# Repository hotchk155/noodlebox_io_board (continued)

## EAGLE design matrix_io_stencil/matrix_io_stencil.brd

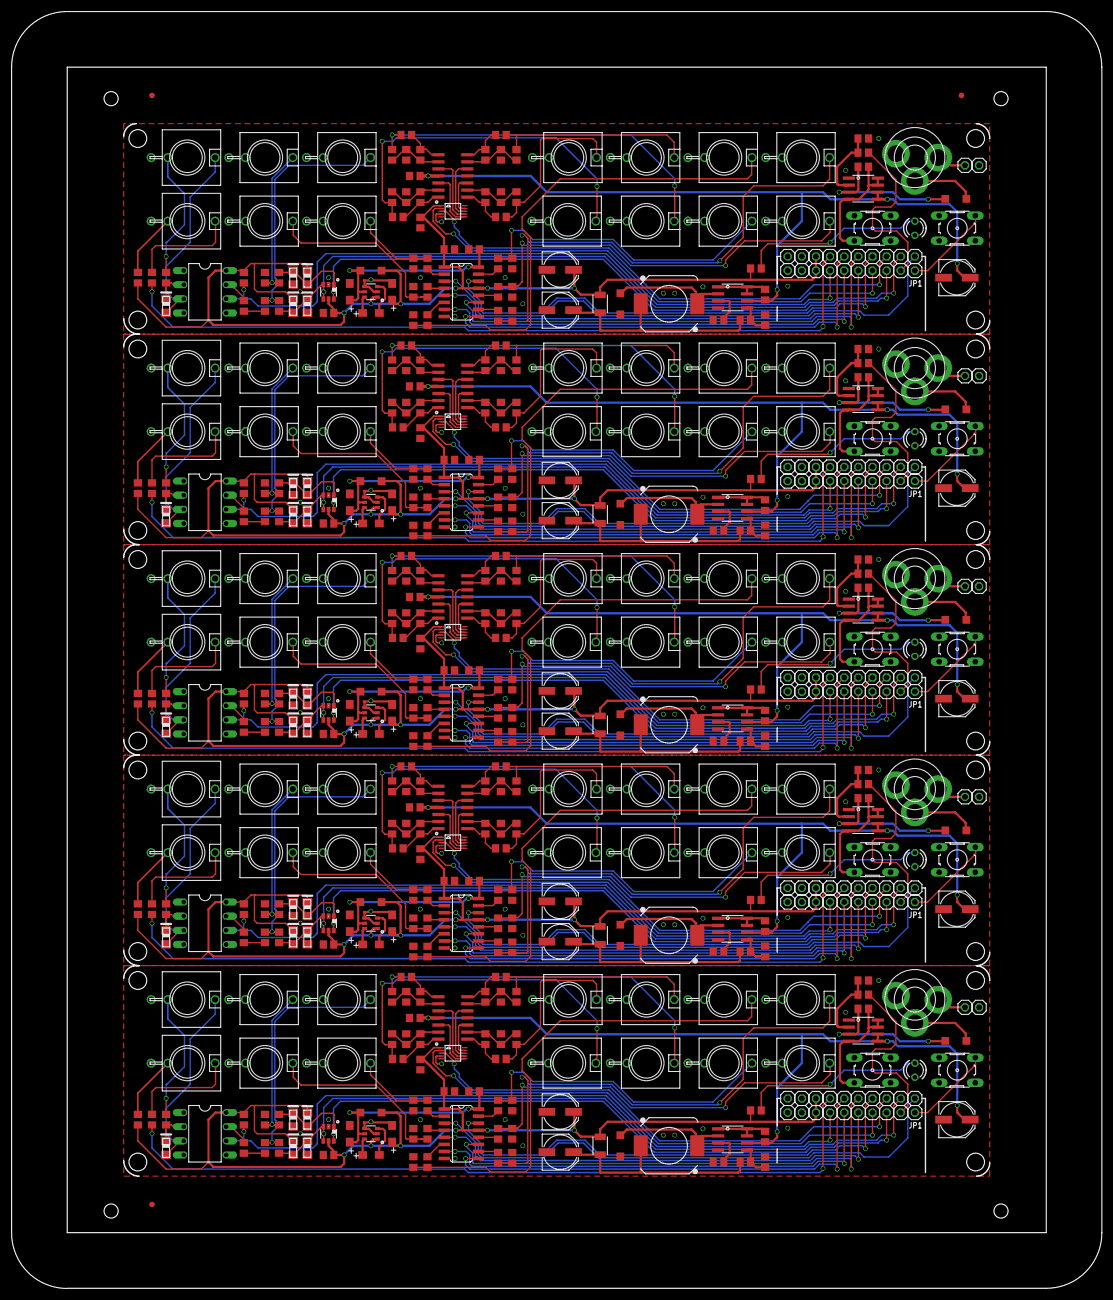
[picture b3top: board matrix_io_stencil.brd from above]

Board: 2 copper layers, 195.9 x 229.5 mm, 573 parts (0 on the bottom side), 345 nets.

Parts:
5V, 5V1, 5V2, 5V3, 5V4, 5V., 5V.1, 5V.2, 5V.3, 5V.4: 1X01
AUXI, AUXI1, AUXI2, AUXI3, AUXI4: WQP-PJ301M-12_JACK
AUXO, AUXO1, AUXO2, AUXO3, AUXO4: WQP-PJ301M-12_JACK
BT+, BT+1, BT+2, BT+3, BT+4: 1X01
BT-, BT-1, BT-2, BT-3, BT-4: 1X01
C1, C8, C9, C18, C24, C31, C32, C34, C46, C53, C54, C56, C68, C75, C76, C78, C90, C97, C98, C100: 100n; C0805
C2, C3, C4, C28, C29, C30, C50, C51, C52, C72, C73, C74, C94, C95, C96: 10u; SMC_A
C5, C6, C7, C10, C11, C12, C39, C40, C41, C42, C43, C44, C61, C62, C63, C64, C65, C66, C83, C84, C85, C86, C87, C88, C105, C106, C107, C108, C109, C110: 10n; C0805
C13, C35, C57, C79, C101: 20p; C0805
C14, C15, C16, C17, C23, C36, C37, C38, C45, C58, C59, C60, C67, C80, C81, C82, C89, C102, C103, C104: C0805
C19, C20, C22, C25, C27, C33, C47, C49, C55, C69, C71, C77, C91, C93, C99: PANASONIC_D
C21, C26, C48, C70, C92: 470p; C0805
CKI, CKI1, CKI2, CKI3, CKI4: WQP-PJ301M-12_JACK
CKO, CKO1, CKO2, CKO3, CKO4: WQP-PJ301M-12_JACK
CKOUT, CKOUT1, CKOUT2, CKOUT3, CKOUT4: 1X01
CLKIN, CLKIN1, CLKIN2, CLKIN3, CLKIN4: 1X01
CVA, CVA1, CVA2, CVA3, CVA4: WQP-PJ301M-12_JACK
CVB, CVB1, CVB2, CVB3, CVB4: WQP-PJ301M-12_JACK
CVC, CVC1, CVC2, CVC3, CVC4: WQP-PJ301M-12_JACK
CVD, CVD1, CVD2, CVD3, CVD4: WQP-PJ301M-12_JACK
D1, D2, D3, D4, D5, D9, D11, D12, D14, D15, D17, D19, D20, D22, D23, D25, D27, D28, D30, D31, D33, D35, D36, D38, D39: 0805DIODE
D6, D7, D8, D10, D13, D16, D18, D21, D24, D26, D29, D32, D34, D37, D40: MBR0520LT; SOD123
DC, DC1, DC2, DC3, DC4: PWR_SOCKET_2_1MM
E$1, E$2, E$3: FIDUCIAL_1MM
G1, G2, G3, G4, G5, G6, G7, G8, G9, G10, G11, G12, G13, G14, G15, G16, G17, G18, G19, G20: 1X01
GD1, GD2, GD3, GD4, GD5, GD6, GD7, GD8, GD9, GD10, GD11, GD12, GD13, GD14, GD15, GD16, GD17, GD18, GD19, GD20: 1X01
GT1, GT2, GT3, GT4, GT5, GT6, GT7, GT8, GT9, GT10, GT11, GT12, GT13, GT14, GT15, GT16, GT17, GT18, GT19, GT20: WQP-PJ301M-12_JACK
IC1, IC10, IC18, IC26, IC34: 6N138; DIL08
IC2, IC16, IC24, IC32, IC40: SN74LVC2G14; DBV_R-PDSO-G6
IC3, IC13, IC21, IC29, IC37: LM27675M5_CHARGEPUMP; SOT23-6
IC4, IC9, IC17, IC25, IC33: LM324D; SO14
IC5, IC11, IC19, IC27, IC35: MCP4728_QUAD_DAC; MSOP10
IC6, IC14, IC22, IC30, IC38: 4504D; SO16
IC7, IC12, IC20, IC28, IC36: SP34063A_BOOST_REG; SOIC8
IC8, IC15, IC23, IC31, IC39: FDS8958B; SOIC8
L1, L3, L5, L7, L9: 1210
L2, L4, L6, L8, L10: DR1030
MIDIIN, MIDIIN1, MIDIIN2, MIDIIN3, MIDIIN4: THONKICONN_STEREO; WQP-PJ301M-ST
MIDIOUT, MIDIOUT1, MIDIOUT2, MIDIOUT3, MIDIOUT4: THONKICONN_STEREO; WQP-PJ301M-ST
OFF, OFF1, OFF2, OFF3, OFF4: B3F-10XX
OFFSW, OFFSW1, OFFSW2, OFFSW3, OFFSW4: 1X01
ON, ON1, ON2, ON3, ON4: B3F-10XX
PWR, PWR1, PWR2, PWR3, PWR4: LED3MM
PWRCTL, PWRCTL1, PWRCTL2, PWRCTL3, PWRCTL4: 1X01
R1, R2, R3, R35, R38, R39, R69, R72, R73, R103, R106, R107, R137, R140, R141: 220; R0805
R4, R5, R36, R37, R70, R71, R104, R105, R138, R139: 1k8; R0805
R6, R8, R65, R68, R99, R102, R133, R136, R167, R170: 100k; R0805
R7, R9, R10, R11, R12, R13, R14, R15, R16, R19, R24, R27, R28, R30, R33, R40, R41, R42, R43, R53, R55, R56, R57, R58, R59, R60, R61, R63, R66, R67, R74, R75, R76, R77, R87, R89, R90, R91, R92, R93, R94, R95, R97, R100, R101, R108, R109, R110, R111, R121, R123, R124, R125, R126, R127, R128, R129, R131, R134, R135, R142, R143, R144, R145, R155, R157, R158, R159, R160, R161, R162, R163, R165, R168, R169: 1k; R0805
R17, R18, R20, R21, R22, R23, R25, R26, R44, R45, R46, R47, R48, R49, R50, R51, R78, R79, R80, R81, R82, R83, R84, R85, R112, R113, R114, R115, R116, R117, R118, R119, R146, R147, R148, R149, R150, R151, R152, R153: 10k/0.1%; R0805
R29, R52, R86, R120, R154: 0r33; R0805
R31, R54, R88, R122, R156: 3k; R0805
R32, R34, R62, R64, R96, R98, R130, R132, R164, R166: 10k; R0805
RSIN, RSIN1, RSIN2, RSIN3, RSIN4: 1X01
RSOUT, RSOUT1, RSOUT2, RSOUT3, RSOUT4: 1X01
RX, RX1, RX2, RX3, RX4: 1X01
SCL, SCL1, SCL2, SCL3, SCL4: 1X01
SDA, SDA1, SDA2, SDA3, SDA4: 1X01
TX, TX1, TX2, TX3, TX4: 1X01

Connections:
+5V: 5V.1, 5V..1, C1.1, C4.+, C8.1, C18.1, C19.+, D3.A, D4.A, D6.A, IC1.8, IC2.5, IC3.1, IC5.1, IC6.1, IC6.13, L1.2, R1.2, R4.2, R28.1
+5V1: 5V1.1, 5V.1.1, C24.1, C30.+, C31.1, C33.+, C34.1, D10.A, D11.A, D14.A, IC10.8, IC11.1, IC13.1, IC14.1, IC14.13, IC16.5, L3.2, R37.2, R38.2, R61.1
+5V2: 5V2.1, 5V.2.1, C46.1, C52.+, C53.1, C55.+, C56.1, D18.A, D19.A, D22.A, IC18.8, IC19.1, IC21.1, IC22.1, IC22.13, IC24.5, L5.2, R71.2, R72.2, R95.1
+5V3: 5V3.1, 5V.3.1, C68.1, C74.+, C75.1, C77.+, C78.1, D26.A, D27.A, D30.A, IC26.8, IC27.1, IC29.1, IC30.1, IC30.13, IC32.5, L7.2, R105.2, R106.2, R129.1
+5V4: 5V4.1, 5V.4.1, C90.1, C96.+, C97.1, C99.+, C100.1, D34.A, D35.A, D38.A, IC34.8, IC35.1, IC37.1, IC38.1, IC38.13, IC40.5, L9.2, R139.2, R140.2, R163.1
+9V: C14.1, C22.+, IC4.4, IC7.6, IC8.5, IC8.6, R29.1
+9V1: C23.1, C25.+, IC9.4, IC12.6, IC15.5, IC15.6, R52.1
+9V2: C45.1, C47.+, IC17.4, IC20.6, IC23.5, IC23.6, R86.1
+9V3: C67.1, C69.+, IC25.4, IC28.6, IC31.5, IC31.6, R120.1
+9V4: C89.1, C91.+, IC33.4, IC36.6, IC39.5, IC39.6, R154.1
+10V: C2.+, C9.2, D6.C, IC3.5, IC6.16
+10V1: C29.+, C32.2, D10.C, IC13.5, IC14.16
+10V2: C51.+, C54.2, D18.C, IC21.5, IC22.16
+10V3: C73.+, C76.2, D26.C, IC29.5, IC30.16
+10V4: C95.+, C98.2, D34.C, IC37.5, IC38.16
AUXGATE: IC6.9, RSOUT.1
AUXGATE1: IC14.9, RSOUT1.1
AUXGATE2: IC22.9, RSOUT2.1
AUXGATE3: IC30.9, RSOUT3.1
AUXGATE4: IC38.9, RSOUT4.1
CLKOUT: CKOUT.1, IC6.3
CLKOUT1: CKOUT1.1, IC14.3
CLKOUT2: CKOUT2.1, IC22.3
CLKOUT3: CKOUT3.1, IC30.3
CLKOUT4: CKOUT4.1, IC38.3
GATE1: G3.1, IC6.14
GATE2: G2.1, IC6.5
GATE3: G1.1, IC6.7
GATE4: G4.1, IC6.11
GATE5: G5.1, IC14.14
GATE6: G6.1, IC14.5
GATE7: G7.1, IC14.7
GATE8: G8.1, IC14.11
GATE9: G9.1, IC22.14
GATE10: G10.1, IC22.5
GATE11: G11.1, IC22.7
GATE12: G12.1, IC22.11
GATE13: G13.1, IC30.14
GATE14: G14.1, IC30.5
GATE15: G15.1, IC30.7
GATE16: G16.1, IC30.11
GATE17: G17.1, IC38.14
GATE18: G18.1, IC38.5
GATE19: G19.1, IC38.7
GATE20: G20.1, IC38.11
GND: AUXI.P$3, AUXO.P$3, BT-.1, C1.2, C2.-, C4.-, C5.1, C6.1, C7.1, C8.2, C9.1, C10.1, C11.1, C12.1, C14.2, C18.2, C19.-, C20.-, C21.2, C22.-, CKI.P$3, CKO.P$3, CVA.P$3, CVB.P$3, CVC.P$3, CVD.P$3, D2.C, D5.C, D7.A, DC.PIN, GD1.1, GD2.1, GD3.1, GD4.1, GT1.P$3, GT2.P$3, GT3.P$3, GT4.P$3, IC1.5, IC2.2, IC3.2, IC3.4, IC4.11, IC5.4, IC5.10, IC6.8, IC7.4, IC8.1, MIDIOUT.P$3, OFF.3, ON.3, PWR.K, R5.2, R6.1, R8.1, R18.1, R20.1, R22.1, R26.1, R30.1, R32.1
GND1: AUXI1.P$3, AUXO1.P$3, BT-1.1, C23.2, C24.2, C25.-, C26.2, C27.-, C29.-, C30.-, C31.2, C32.1, C33.-, C34.2, C39.1, C40.1, C41.1, C42.1, C43.1, C44.1, CKI1.P$3, CKO1.P$3, CVA1.P$3, CVB1.P$3, CVC1.P$3, CVD1.P$3, D12.C, D15.C, D16.A, DC1.PIN, GD5.1, GD6.1, GD7.1, GD8.1, GT5.P$3, GT6.P$3, GT7.P$3, GT8.P$3, IC9.11, IC10.5, IC11.4, IC11.10, IC12.4, IC13.2, IC13.4, IC14.8, IC15.1, IC16.2, MIDIOUT1.P$3, OFF1.3, ON1.3, PWR1.K, R36.2, R48.1, R49.1, R50.1, R51.1, R53.1, R64.1, R65.1, R68.1
GND2: AUXI2.P$3, AUXO2.P$3, BT-2.1, C45.2, C46.2, C47.-, C48.2, C49.-, C51.-, C52.-, C53.2, C54.1, C55.-, C56.2, C61.1, C62.1, C63.1, C64.1, C65.1, C66.1, CKI2.P$3, CKO2.P$3, CVA2.P$3, CVB2.P$3, CVC2.P$3, CVD2.P$3, D20.C, D23.C, D24.A, DC2.PIN, GD9.1, GD10.1, GD11.1, GD12.1, GT9.P$3, GT10.P$3, GT11.P$3, GT12.P$3, IC17.11, IC18.5, IC19.4, IC19.10, IC20.4, IC21.2, IC21.4, IC22.8, IC23.1, IC24.2, MIDIOUT2.P$3, OFF2.3, ON2.3, PWR2.K, R70.2, R82.1, R83.1, R84.1, R85.1, R87.1, R98.1, R99.1, R102.1
GND3: AUXI3.P$3, AUXO3.P$3, BT-3.1, C67.2, C68.2, C69.-, C70.2, C71.-, C73.-, C74.-, C75.2, C76.1, C77.-, C78.2, C83.1, C84.1, C85.1, C86.1, C87.1, C88.1, CKI3.P$3, CKO3.P$3, CVA3.P$3, CVB3.P$3, CVC3.P$3, CVD3.P$3, D28.C, D31.C, D32.A, DC3.PIN, GD13.1, GD14.1, GD15.1, GD16.1, GT13.P$3, GT14.P$3, GT15.P$3, GT16.P$3, IC25.11, IC26.5, IC27.4, IC27.10, IC28.4, IC29.2, IC29.4, IC30.8, IC31.1, IC32.2, MIDIOUT3.P$3, OFF3.3, ON3.3, PWR3.K, R104.2, R116.1, R117.1, R118.1, R119.1, R121.1, R132.1, R133.1, R136.1
GND4: AUXI4.P$3, AUXO4.P$3, BT-4.1, C89.2, C90.2, C91.-, C92.2, C93.-, C95.-, C96.-, C97.2, C98.1, C99.-, C100.2, C105.1, C106.1, C107.1, C108.1, C109.1, C110.1, CKI4.P$3, CKO4.P$3, CVA4.P$3, CVB4.P$3, CVC4.P$3, CVD4.P$3, D36.C, D39.C, D40.A, DC4.PIN, GD17.1, GD18.1, GD19.1, GD20.1, GT17.P$3, GT18.P$3, GT19.P$3, GT20.P$3, IC33.11, IC34.5, IC35.4, IC35.10, IC36.4, IC37.2, IC37.4, IC38.8, IC39.1, IC40.2, MIDIOUT4.P$3, OFF4.3, ON4.3, PWR4.K, R138.2, R150.1, R151.1, R152.1, R153.1, R155.1, R166.1, R167.1, R170.1
MIDI_IN: IC1.6, R4.1, RX.1
MIDI_IN1: IC10.6, R37.1, RX1.1
MIDI_IN2: IC18.6, R71.1, RX2.1
MIDI_IN3: IC26.6, R105.1, RX3.1
MIDI_IN4: IC34.6, R139.1, RX4.1
MIDI_OUT: R2.2, TX.1
MIDI_OUT1: R39.2, TX1.1
MIDI_OUT2: R73.2, TX2.1
MIDI_OUT3: R107.2, TX3.1
MIDI_OUT4: R141.2, TX4.1
unnamed: MIDIOUT.P$2, R1.1
unnamed: D1.A, IC1.2, R3.2
unnamed: IC4.3, IC5.7
unnamed: D1.C, IC1.3, MIDIIN.P$1
unnamed: IC1.7, R5.1
unnamed: MIDIOUT.P$1, R2.1
unnamed: MIDIIN.P$2, R3.1
unnamed: CVC.P$1, R16.2, R17.2
unnamed: CVD.P$1, R25.2, R27.2
unnamed: CVB.P$1, R19.2, R21.2
unnamed: CVA.P$1, R23.2, R24.2
unnamed: C13.2, IC4.1, R16.1
unnamed: C15.2, IC4.7, R27.1
unnamed: C17.2, IC4.8, R24.1
unnamed: C16.2, IC4.14, R19.1
unnamed: BT+.1, DC.NC
unnamed: C16.1, IC4.13, R20.2, R21.1
unnamed: C17.1, IC4.9, R22.2, R23.1
unnamed: IC6.10, R15.1
unnamed: C15.1, IC4.6, R25.1, R26.2
unnamed: D9.A, IC10.2, R35.2
unnamed: C13.1, IC4.2, R17.1, R18.2
unnamed: CLKIN.1, IC2.6
unnamed: AUXI.P$1, R8.2, R9.2
unnamed: IC2.4, RSIN.1
unnamed: D4.C, D5.A, IC2.3, R9.1
unnamed: C12.2, GT2.P$1, R15.2
unnamed: D9.C, IC10.3, MIDIIN1.P$1
unnamed: IC4.5, IC5.6
unnamed: IC4.10, IC5.9
unnamed: IC4.12, IC5.8
unnamed: IC7.1, IC7.7, IC7.8, R29.2
unnamed: IC7.5, R30.2, R31.2
unnamed: C21.1, IC7.3
unnamed: D7.C, IC7.2, L2.2
unnamed: D8.A, DC.BARREL
unnamed: IC6.2, R10.1
unnamed: C3.+, IC3.6
unnamed: C3.-, IC3.3
unnamed: IC6.4, R11.1
unnamed: IC6.6, R12.1
unnamed: IC10.7, R36.1
unnamed: IC6.12, R14.1
unnamed: AUXO.P$1, C5.2, R10.2
unnamed: C6.2, CKO.P$1, R11.2
unnamed: C7.2, GT1.P$1, R12.2
unnamed: C11.2, GT4.P$1, R14.2
unnamed: C10.2, GT3.P$1, R13.2
unnamed: IC6.15, R13.1
unnamed: MIDIOUT1.P$1, R39.1
unnamed: C20.+, L1.1, L2.1, R31.1
unnamed: CVC1.P$1, R40.2, R44.2
unnamed: D2.A, D3.C, IC2.1, R7.1
unnamed: CKI.P$1, R6.2, R7.2
unnamed: CVD1.P$1, R41.2, R45.2
unnamed: PWR.A, R28.2
unnamed: C35.2, IC9.1, R40.1
unnamed: C36.2, IC9.7, R41.1
unnamed: C37.2, IC9.8, R42.1
unnamed: C38.2, IC9.14, R43.1
unnamed: IC8.4, IC8.7, IC8.8, ON.2, R34.2
unnamed: IC8.2, R32.2, R33.2
unnamed: C38.1, IC9.13, R47.1, R51.2
unnamed: C37.1, IC9.9, R46.1, R50.2
unnamed: C36.1, IC9.6, R45.1, R49.2
unnamed: C35.1, IC9.2, R44.1, R48.2
unnamed: IC9.10, IC11.9
unnamed: IC9.12, IC11.8
unnamed: IC12.1, IC12.7, IC12.8, R52.2
unnamed: C26.1, IC12.3
unnamed: D16.C, IC12.2, L4.2
unnamed: IC12.5, R53.2, R54.2
unnamed: C28.+, IC13.6
unnamed: C28.-, IC13.3
unnamed: D13.A, DC1.BARREL
unnamed: CVB1.P$1, R43.2, R47.2
unnamed: CVA1.P$1, R42.2, R46.2
unnamed: IC14.2, R55.1
unnamed: IC14.4, R56.1
unnamed: IC14.6, R57.1
unnamed: IC14.12, R58.1
unnamed: AUXO1.P$1, C39.2, R55.2
unnamed: C40.2, CKO1.P$1, R56.2
unnamed: C41.2, GT6.P$1, R57.2
unnamed: C42.2, GT7.P$1, R58.2
unnamed: C43.2, GT8.P$1, R59.2
unnamed: IC14.15, R59.1
unnamed: D11.C, D12.A, IC16.1, R60.1
unnamed: CKI1.P$1, R60.2, R65.2
unnamed: PWR1.A, R61.2
unnamed: IC15.4, IC15.7, IC15.8, ON1.2, R62.2
unnamed: IC15.2, R63.2, R64.2
unnamed: IC9.3, IC11.7
unnamed: IC9.5, IC11.6
unnamed: C27.+, L3.1, L4.1, R54.1
unnamed: MIDIIN1.P$2, R35.1
unnamed: MIDIOUT1.P$2, R38.1
unnamed: BT+1.1, DC1.NC
unnamed: IC14.10, R66.1
unnamed: AUXI1.P$1, R67.2, R68.2
unnamed: D14.C, D15.A, IC16.3, R67.1
unnamed: IC16.4, RSIN1.1
unnamed: CLKIN1.1, IC16.6
unnamed: C44.2, GT5.P$1, R66.2
unnamed: D17.A, IC18.2, R69.2
unnamed: D17.C, IC18.3, MIDIIN2.P$1
unnamed: IC18.7, R70.1
unnamed: MIDIOUT2.P$1, R73.1
unnamed: CVC2.P$1, R74.2, R78.2
unnamed: CVD2.P$1, R75.2, R79.2
unnamed: C57.2, IC17.1, R74.1
unnamed: C58.2, IC17.7, R75.1
unnamed: C59.2, IC17.8, R76.1
unnamed: C60.2, IC17.14, R77.1
unnamed: C60.1, IC17.13, R81.1, R85.2
unnamed: C59.1, IC17.9, R80.1, R84.2
unnamed: C58.1, IC17.6, R79.1, R83.2
unnamed: C57.1, IC17.2, R78.1, R82.2
unnamed: IC17.10, IC19.9
unnamed: IC17.12, IC19.8
unnamed: IC20.1, IC20.7, IC20.8, R86.2
unnamed: C48.1, IC20.3
unnamed: D24.C, IC20.2, L6.2
unnamed: IC20.5, R87.2, R88.2
unnamed: C50.+, IC21.6
unnamed: C50.-, IC21.3
unnamed: D21.A, DC2.BARREL
unnamed: CVB2.P$1, R77.2, R81.2
unnamed: CVA2.P$1, R76.2, R80.2
unnamed: IC22.2, R89.1
unnamed: IC22.4, R90.1
unnamed: IC22.6, R91.1
unnamed: IC22.12, R92.1
unnamed: AUXO2.P$1, C61.2, R89.2
unnamed: C62.2, CKO2.P$1, R90.2
unnamed: C63.2, GT10.P$1, R91.2
unnamed: C64.2, GT11.P$1, R92.2
unnamed: C65.2, GT12.P$1, R93.2
unnamed: IC22.15, R93.1
unnamed: D19.C, D20.A, IC24.1, R94.1
unnamed: CKI2.P$1, R94.2, R99.2
unnamed: PWR2.A, R95.2
unnamed: IC23.4, IC23.7, IC23.8, ON2.2, R96.2
unnamed: IC23.2, R97.2, R98.2
unnamed: IC17.3, IC19.7
unnamed: IC17.5, IC19.6
unnamed: C49.+, L5.1, L6.1, R88.1
unnamed: MIDIIN2.P$2, R69.1
unnamed: MIDIOUT2.P$2, R72.1
unnamed: BT+2.1, DC2.NC
unnamed: IC22.10, R100.1
unnamed: AUXI2.P$1, R101.2, R102.2
unnamed: D22.C, D23.A, IC24.3, R101.1
unnamed: IC24.4, RSIN2.1
unnamed: CLKIN2.1, IC24.6
unnamed: C66.2, GT9.P$1, R100.2
unnamed: D25.A, IC26.2, R103.2
unnamed: D25.C, IC26.3, MIDIIN3.P$1
unnamed: IC26.7, R104.1
unnamed: MIDIOUT3.P$1, R107.1
unnamed: CVC3.P$1, R108.2, R112.2
unnamed: CVD3.P$1, R109.2, R113.2
unnamed: C79.2, IC25.1, R108.1
unnamed: C80.2, IC25.7, R109.1
unnamed: C81.2, IC25.8, R110.1
unnamed: C82.2, IC25.14, R111.1
unnamed: C82.1, IC25.13, R115.1, R119.2
unnamed: C81.1, IC25.9, R114.1, R118.2
unnamed: C80.1, IC25.6, R113.1, R117.2
unnamed: C79.1, IC25.2, R112.1, R116.2
unnamed: IC25.10, IC27.9
unnamed: IC25.12, IC27.8
unnamed: IC28.1, IC28.7, IC28.8, R120.2
unnamed: C70.1, IC28.3
unnamed: D32.C, IC28.2, L8.2
unnamed: IC28.5, R121.2, R122.2
unnamed: C72.+, IC29.6
unnamed: C72.-, IC29.3
unnamed: D29.A, DC3.BARREL
unnamed: CVB3.P$1, R111.2, R115.2
unnamed: CVA3.P$1, R110.2, R114.2
unnamed: IC30.2, R123.1
unnamed: IC30.4, R124.1
unnamed: IC30.6, R125.1
unnamed: IC30.12, R126.1
unnamed: AUXO3.P$1, C83.2, R123.2
unnamed: C84.2, CKO3.P$1, R124.2
unnamed: C85.2, GT14.P$1, R125.2
unnamed: C86.2, GT15.P$1, R126.2
unnamed: C87.2, GT16.P$1, R127.2
unnamed: IC30.15, R127.1
unnamed: D27.C, D28.A, IC32.1, R128.1
unnamed: CKI3.P$1, R128.2, R133.2
unnamed: PWR3.A, R129.2
unnamed: IC31.4, IC31.7, IC31.8, ON3.2, R130.2
unnamed: IC31.2, R131.2, R132.2
unnamed: IC25.3, IC27.7
unnamed: IC25.5, IC27.6
unnamed: C71.+, L7.1, L8.1, R122.1
unnamed: MIDIIN3.P$2, R103.1
unnamed: MIDIOUT3.P$2, R106.1
unnamed: BT+3.1, DC3.NC
unnamed: IC30.10, R134.1
unnamed: AUXI3.P$1, R135.2, R136.2
unnamed: D30.C, D31.A, IC32.3, R135.1
unnamed: IC32.4, RSIN3.1
unnamed: CLKIN3.1, IC32.6
unnamed: C88.2, GT13.P$1, R134.2
unnamed: D33.A, IC34.2, R137.2
unnamed: D33.C, IC34.3, MIDIIN4.P$1
unnamed: IC34.7, R138.1
unnamed: MIDIOUT4.P$1, R141.1
unnamed: CVC4.P$1, R142.2, R146.2
unnamed: CVD4.P$1, R143.2, R147.2
unnamed: C101.2, IC33.1, R142.1
unnamed: C102.2, IC33.7, R143.1
unnamed: C103.2, IC33.8, R144.1
unnamed: C104.2, IC33.14, R145.1
unnamed: C104.1, IC33.13, R149.1, R153.2
unnamed: C103.1, IC33.9, R148.1, R152.2
unnamed: C102.1, IC33.6, R147.1, R151.2
unnamed: C101.1, IC33.2, R146.1, R150.2
unnamed: IC33.10, IC35.9
unnamed: IC33.12, IC35.8
unnamed: IC36.1, IC36.7, IC36.8, R154.2
unnamed: C92.1, IC36.3
unnamed: D40.C, IC36.2, L10.2
unnamed: IC36.5, R155.2, R156.2
unnamed: C94.+, IC37.6
unnamed: C94.-, IC37.3
unnamed: D37.A, DC4.BARREL
unnamed: CVB4.P$1, R145.2, R149.2
unnamed: CVA4.P$1, R144.2, R148.2
unnamed: IC38.2, R157.1
unnamed: IC38.4, R158.1
unnamed: IC38.6, R159.1
unnamed: IC38.12, R160.1
unnamed: AUXO4.P$1, C105.2, R157.2
unnamed: C106.2, CKO4.P$1, R158.2
unnamed: C107.2, GT18.P$1, R159.2
unnamed: C108.2, GT19.P$1, R160.2
unnamed: C109.2, GT20.P$1, R161.2
unnamed: IC38.15, R161.1
unnamed: D35.C, D36.A, IC40.1, R162.1
unnamed: CKI4.P$1, R162.2, R167.2
unnamed: PWR4.A, R163.2
unnamed: IC39.4, IC39.7, IC39.8, ON4.2, R164.2
unnamed: IC39.2, R165.2, R166.2
unnamed: IC33.3, IC35.7
unnamed: IC33.5, IC35.6
unnamed: C93.+, L9.1, L10.1, R156.1
unnamed: MIDIIN4.P$2, R137.1
unnamed: MIDIOUT4.P$2, R140.1
unnamed: BT+4.1, DC4.NC
unnamed: IC38.10, R168.1
unnamed: AUXI4.P$1, R169.2, R170.2
unnamed: D38.C, D39.A, IC40.3, R169.1
unnamed: IC40.4, RSIN4.1
unnamed: CLKIN4.1, IC40.6
unnamed: C110.2, GT17.P$1, R168.2
OFF_SW: OFF.2, OFFSW.1
OFF_SW1: OFF1.2, OFFSW1.1
OFF_SW2: OFF2.2, OFFSW2.1
OFF_SW3: OFF3.2, OFFSW3.1
OFF_SW4: OFF4.2, OFFSW4.1
PWR_CTRL: PWRCTL.1, R33.1
PWR_CTRL1: PWRCTL1.1, R63.1
PWR_CTRL2: PWRCTL2.1, R97.1
PWR_CTRL3: PWRCTL3.1, R131.1
PWR_CTRL4: PWRCTL4.1, R165.1
SCL: IC5.2, SCL.1
SCL1: IC11.2, SCL1.1
SCL2: IC19.2, SCL2.1
SCL3: IC27.2, SCL3.1
SCL4: IC35.2, SCL4.1
SDA: IC5.3, SDA.1
SDA1: IC11.3, SDA1.1
SDA2: IC19.3, SDA2.1
SDA3: IC27.3, SDA3.1
SDA4: IC35.3, SDA4.1
VIN: D8.C, IC8.3, R34.1
VIN1: D13.C, IC15.3, R62.1
VIN2: D21.C, IC23.3, R96.1
VIN3: D29.C, IC31.3, R130.1
VIN4: D37.C, IC39.3, R164.1

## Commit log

2018-07-10 rename
2019-05-19 changes for rev2
2019-05-27 version 2 ready for fab
2019-05-27 typo fix
2019-11-26 work in progress
2019-11-26 V3 candidate
2020-01-02 values
2020-01-02 use the new stereo Thonk sockets
2020-01-14 V4 ready to go
2020-02-18 V5 first cut
2020-02-19 silk
2020-02-26 V5 READY TO GO
2020-02-26 eagle 6.6
2020-03-30 panel
2022-04-09 asaas
2022-04-22 3v3 updates
2023-02-10 Revert "3v3 updates"
    This reverts commit 782c7fb22120100be74f5025aa682998f87b6e62.
